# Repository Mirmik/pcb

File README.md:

Файлы проектов печатных плат
============================

drive4 - Ардуино-программируемый 4-х канальный драйвер двигателей.

From Mirmik

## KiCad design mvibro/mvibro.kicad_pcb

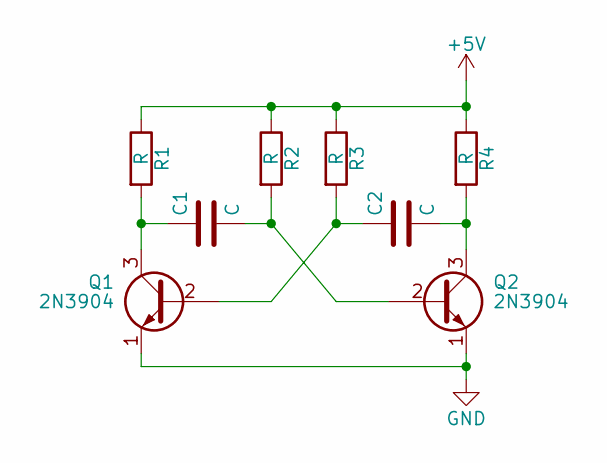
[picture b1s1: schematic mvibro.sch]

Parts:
C1, C2: C; C_Rect_L4.0mm_W2.5mm_P2.50mm
Q1, Q2: 2N3904; TO-92_Molded_Narrow
R1, R2, R3, R4: R; R_Axial_DIN0309_L9.0mm_D3.2mm_P12.70mm_Horizontal

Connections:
+5V: R1.1, R2.1, R3.1, R4.1
GND: Q1.1 (E), Q2.1 (E)
unnamed: C1.1, Q1.3 (C), R1.2
unnamed: C1.2, Q2.2 (B), R2.2
unnamed: C2.1, Q1.2 (B), R3.2
unnamed: C2.2, Q2.3 (C), R4.2

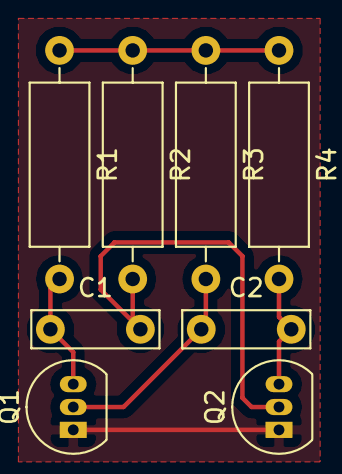
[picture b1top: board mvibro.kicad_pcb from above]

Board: 2 copper layers, 8 parts (0 on the bottom side), 6 nets.

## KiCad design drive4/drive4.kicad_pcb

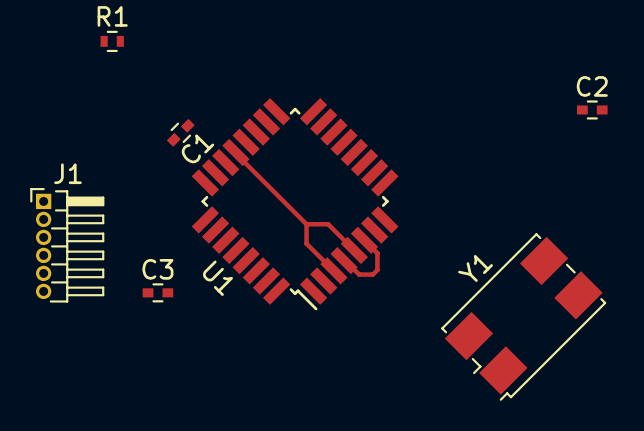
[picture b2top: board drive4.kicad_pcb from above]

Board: 2 copper layers, 7 parts (0 on the bottom side), 9 nets.

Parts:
C1, C2, C3: C; C_0402
J1: FTDI Port; Pin_Header_Angled_1x06_Pitch1.00mm
R1: R; R_0402
U1: ATMEGA328-AU; TQFP-32_7x7mm_Pitch0.8mm
Y1: Crystal_GND2; Crystal_SMD_FOX_FQ7050-4pin_7.0x5.0mm

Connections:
/RESET: C3.2, R1.2, U1.29
DTR: C3.1, J1.6
GND: C1.2, C2.2, J1.1, J1.2, U1.3, U1.5, U1.21, Y1.2
unnamed: C1.1, U1.20
unnamed: U1.7, Y1.3
unnamed: U1.8, Y1.1
RX: J1.4, U1.30
TX: J1.5, U1.31
VCC: C2.1, J1.3, R1.1, U1.4, U1.6, U1.18

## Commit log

2017-02-18 first
2017-02-18 drive4
